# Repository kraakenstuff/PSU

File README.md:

# PSU

Linear power supply. Consists of two boards - one for transformer, and the other for filtering. One of these filter boards is supposed to distribute power to a single row in the case (voltage regulators should be able to handle 1.5A of current per rail).

Status: finished and tested.

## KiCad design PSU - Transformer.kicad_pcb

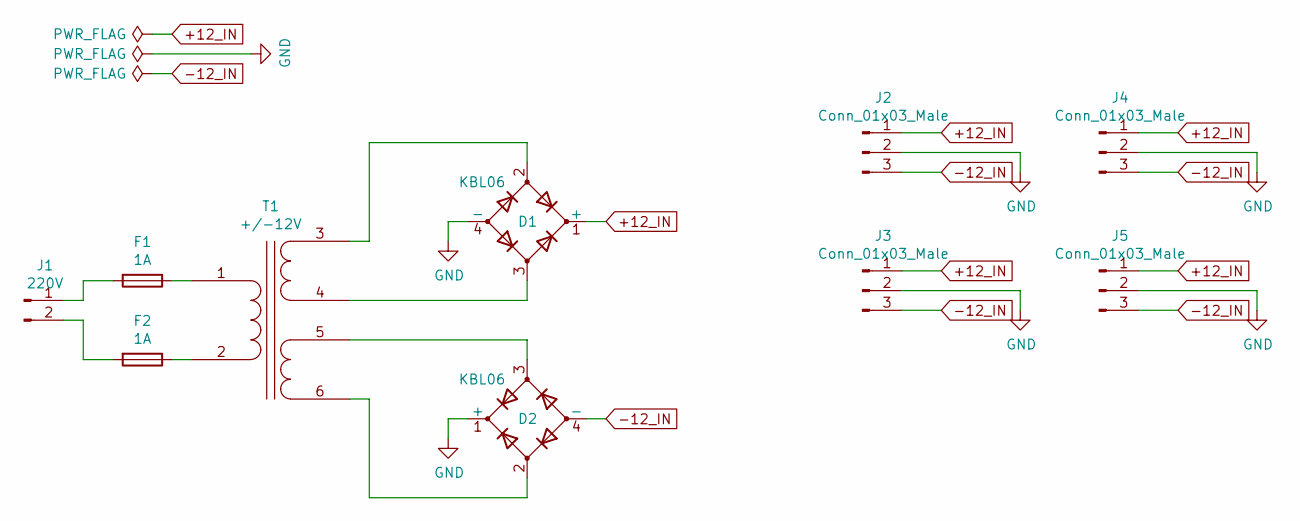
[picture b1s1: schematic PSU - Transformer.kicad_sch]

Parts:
D1, D2: KBL06; Diode_Bridge_18.5x5.5
F1, F2: 1A; Fuseholder5x20_horiz_SemiClosed_Casing10x25mm
J1: 220V; Terminal 2 contacts
J2, J3, J4, J5: Conn_01x03_Male; Klema x3
T1: +/-12V; Toroidal transformer 220V 150VA 2x12V

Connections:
+12_IN: D1.1 (+), J2.1, J3.1, J4.1, J5.1
-12_IN: D2.4 (-), J2.3, J3.3, J4.3, J5.3
GND: D1.4 (-), D2.1 (+), J2.2, J3.2, J4.2, J5.2
unnamed: D1.2, T1.3 (SA)
unnamed: D1.3, T1.4 (SB)
unnamed: D2.2, T1.6 (SD)
unnamed: D2.3, T1.5 (SC)
unnamed: F1.1, T1.1 (AA)
unnamed: F1.2, J1.1
unnamed: F2.1, T1.2 (AB)
unnamed: F2.2, J1.2

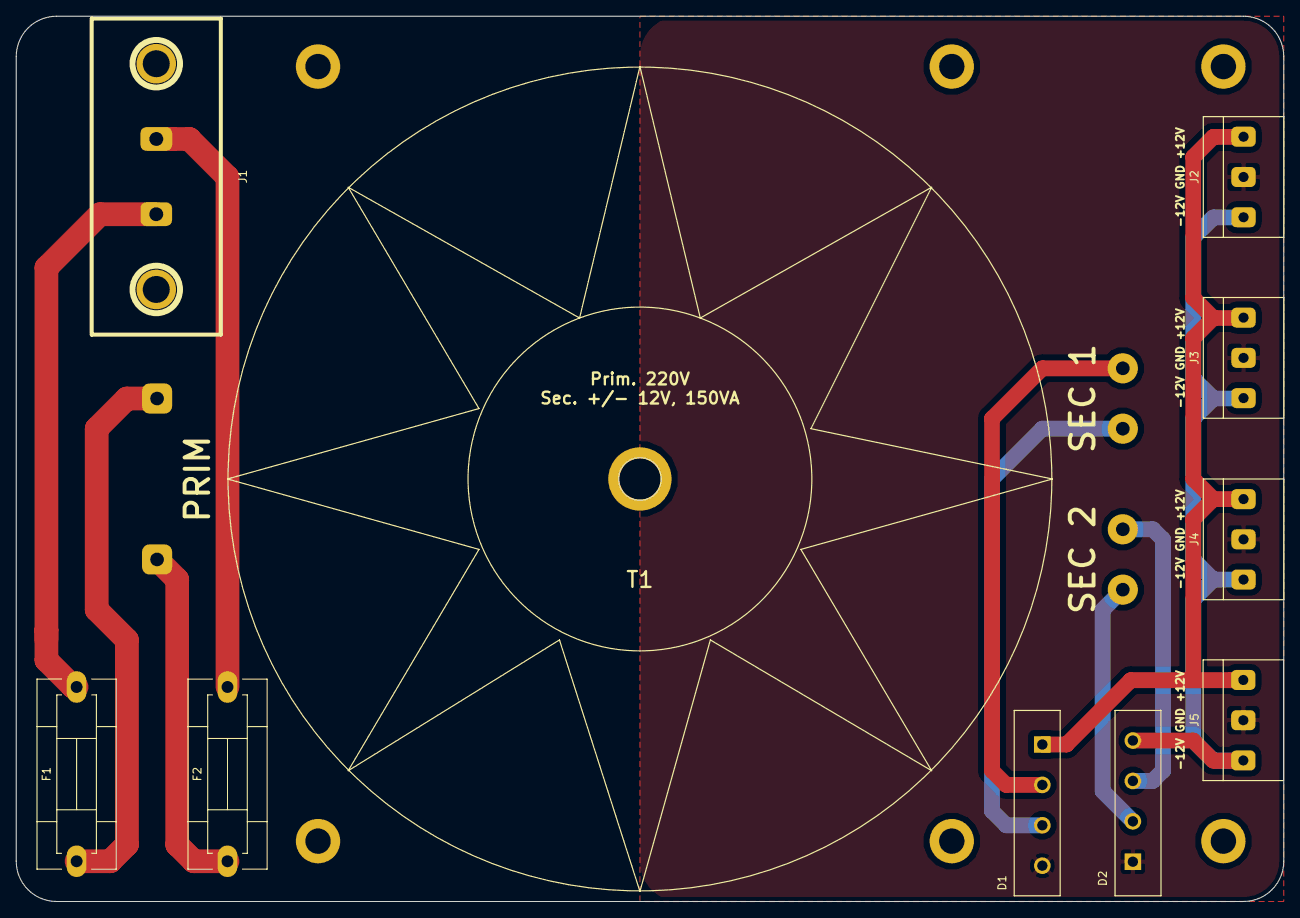
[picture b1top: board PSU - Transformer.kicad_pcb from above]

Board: 2 copper layers, 160.0 x 111.8 mm, 10 parts (0 on the bottom side), 11 nets.

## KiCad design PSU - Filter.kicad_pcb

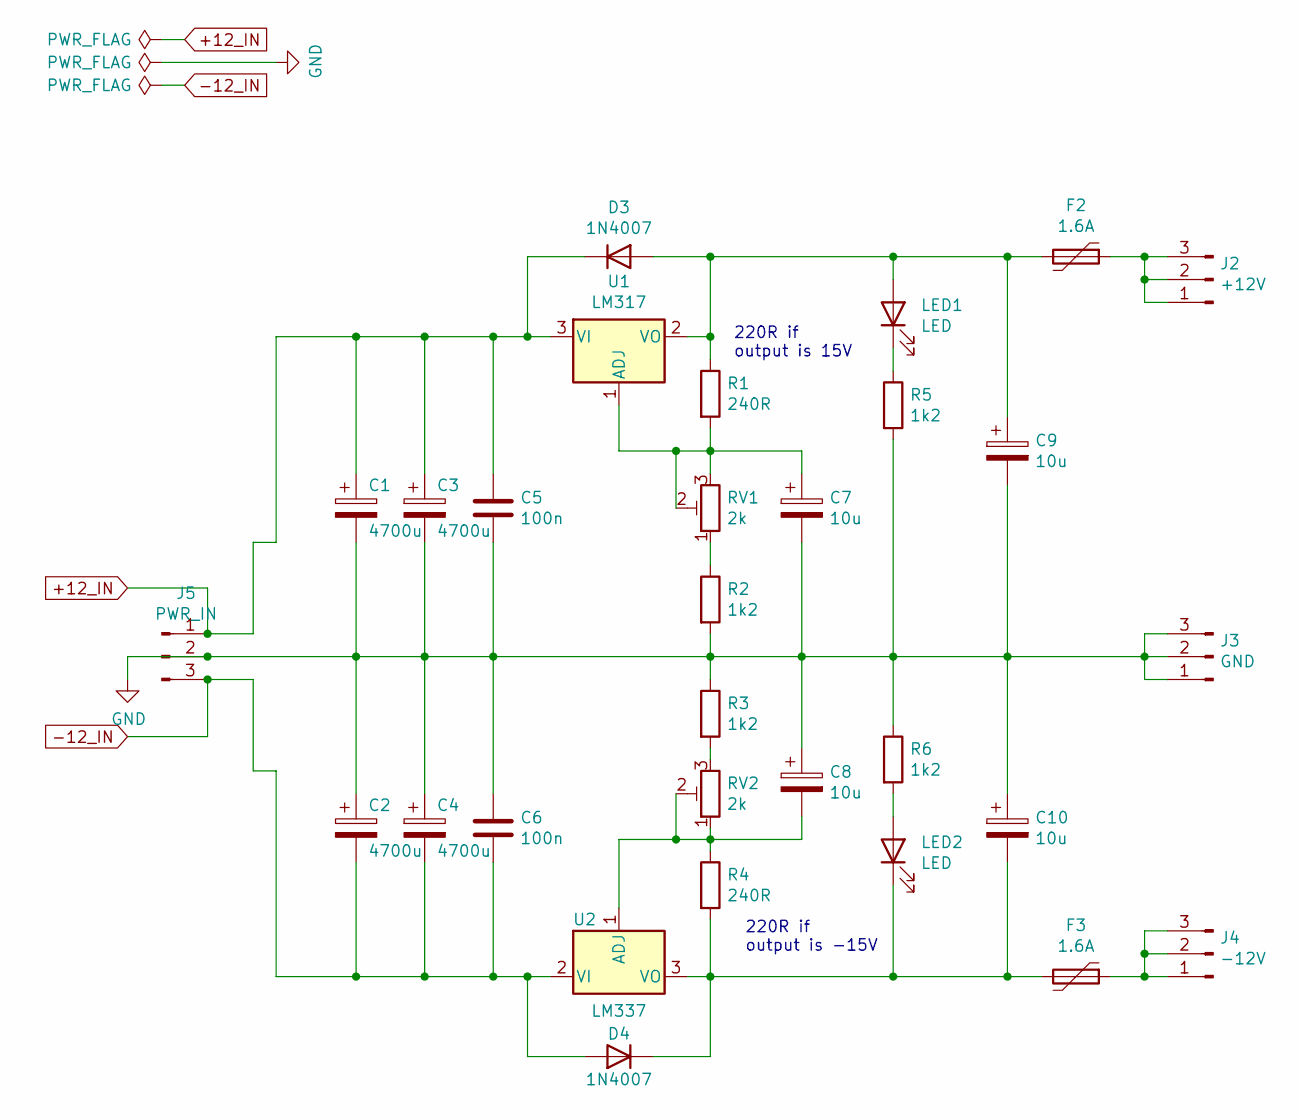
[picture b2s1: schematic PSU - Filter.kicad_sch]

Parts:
C1, C2, C3, C4: 4700u; CP_Radial_D17.0mm_P7.50mm
C5, C6: 100n; C_Rect_L10.0mm_W2.5mm_P7.50mm_MKS4
C7, C8, C9, C10: 10u; CP_Radial_D6.3mm_P2.50mm
D3, D4: 1N4007; D_DO-15_P12.70mm_Horizontal
F2, F3: 1.6A; C_Disc_D6.0mm_W2.5mm_P5.00mm
J2: +12V; Klema x3
J3: GND; Klema x3
J4: -12V; Klema x3
J5: PWR_IN; Klema x3
LED1, LED2: LED; LED_D5.0mm
R1, R4: 240R; R_Axial_DIN0414_L11.9mm_D4.5mm_P15.24mm_Horizontal
R2, R3: 1k2; R_Axial_DIN0414_L11.9mm_D4.5mm_P15.24mm_Horizontal
R5, R6: 1k2; R_Axial_DIN0207_L6.3mm_D2.5mm_P7.62mm_Horizontal
RV1, RV2: 2k; Potentiometer_Bourns_3296W_Vertical
U1: LM317; TO-220-3_Vertical
U2: LM337; TO-220-3

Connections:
+12_IN: C1.1, C3.1, C5.1, D3.1 (K), J5.1, U1.3 (VI); also elsewhere on the board
-12_IN: C2.2, C4.2, C6.2, D4.2 (A), J5.3, U2.2 (VI); also elsewhere on the board
GND: C1.2, C2.1, C3.2, C4.1, C5.2, C6.1, C7.2, C8.1, C9.2, C10.1, J3.1, J3.2, J3.3, J5.2, R2.2, R3.1, R5.2, R6.1; also elsewhere on the board
unnamed: C7.1, R1.2, RV1.2, RV1.3, U1.1 (ADJ)
unnamed: C8.2, R4.1, RV2.1, RV2.2, U2.1 (ADJ)
unnamed: C9.1, D3.2 (A), F2.2, LED1.2 (A), R1.1, U1.2 (VO)
unnamed: C10.2, D4.1 (K), F3.2, LED2.1 (K), R4.2, U2.3 (VO)
unnamed: F2.1, J2.1, J2.2, J2.3
unnamed: F3.1, J4.1, J4.2, J4.3
unnamed: LED1.1 (K), R5.1
unnamed: LED2.2 (A), R6.2
unnamed: R2.1, RV1.1
unnamed: R3.2, RV2.3

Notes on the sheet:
220R if output is -15V
220R if output is 15V

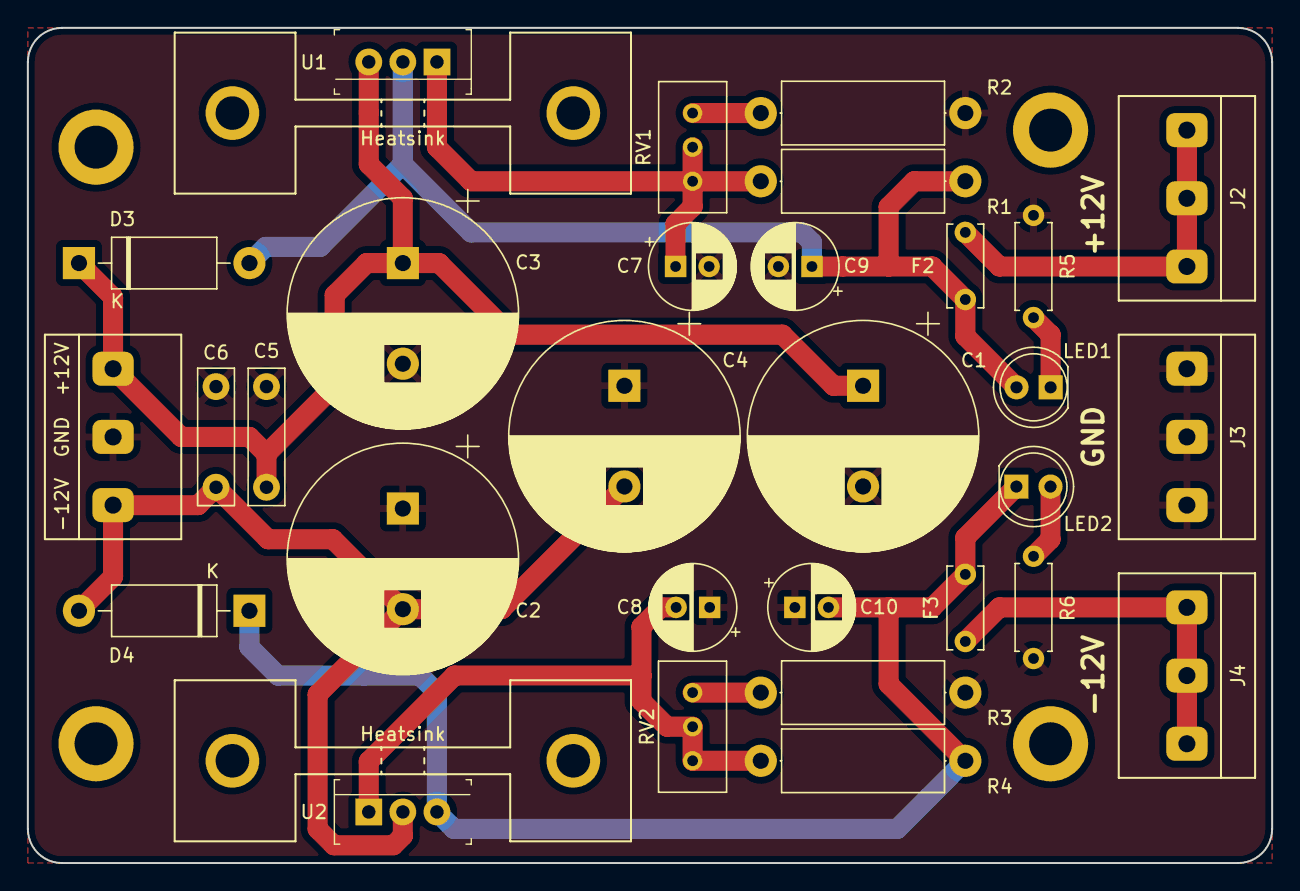
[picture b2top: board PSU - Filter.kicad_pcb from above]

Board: 2 copper layers, 92.7 x 62.2 mm, 32 parts (0 on the bottom side), 13 nets.

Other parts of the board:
-12V  GND  +12V: PWR_IN; Klema x3
Heatsink: ALUMINIJUMSKI HLADNJAK TO-220/25; ALUMINIJUMSKI HLADNJAK TO-220_25
Heatsink#2: ALUMINIJUMSKI HLADNJAK TO-220/25; ALUMINIJUMSKI HLADNJAK TO-220_25

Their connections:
+12_IN: -12V GND +12V.1; also elsewhere on the board
-12_IN: -12V GND +12V.3; also elsewhere on the board
GND: -12V GND +12V.2; also elsewhere on the board

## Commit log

2018-12-02 Release client. Fixed a short in +12 branch Changed 10uF footprint to 6.3/2.5mm New KiCad standard library Pointers to the KraakenStuffLib library
2018-12-02 Fixed library dependencies
2019-03-08 Finished. First round of testing passed
2019-07-24 Made more space between caps and heatsinks on the filter board
2019-07-24 Fixed gerber files
2019-07-24 Added a label to the input of filter board
2022-03-05 Adapted for KiCad6. Also fixed an error in silkscreen for the filter
